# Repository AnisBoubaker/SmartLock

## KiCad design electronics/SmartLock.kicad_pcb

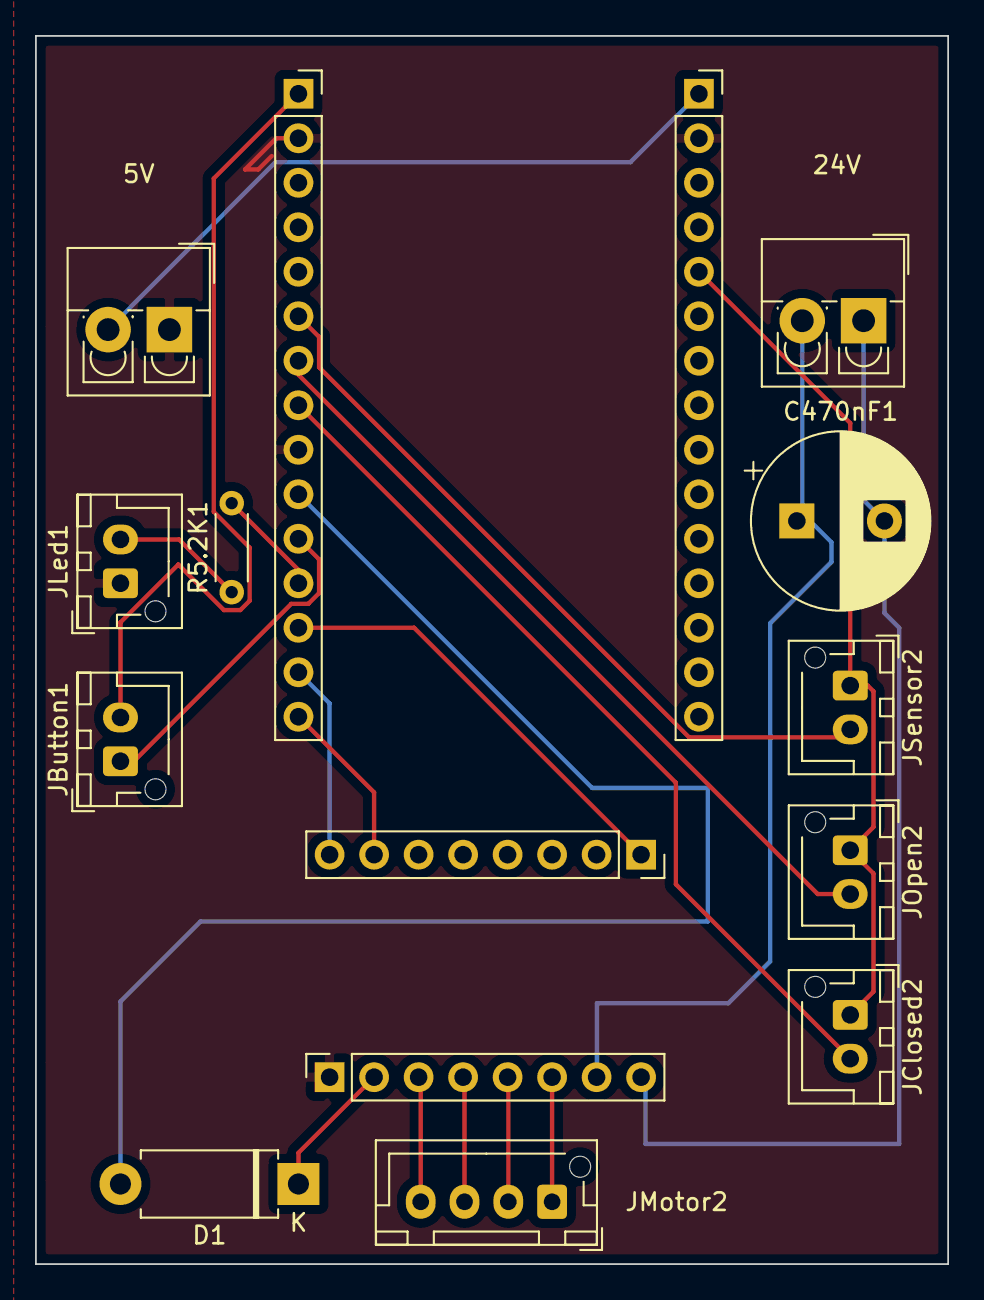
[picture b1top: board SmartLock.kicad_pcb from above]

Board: 2 copper layers, 52.1 x 70.1 mm, 15 parts (0 on the bottom side), 21 nets.

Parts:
5V: 5V; TerminalBlock_4Ucon_1x02_P3.50mm_Vertical
24V: 24V; TerminalBlock_4Ucon_1x02_P3.50mm_Vertical
C470nF1: CP; CP_Radial_D10.0mm_P5.00mm
D1: D_Zener; D_DO-15_P10.16mm_Horizontal
JButton1: Button; JST_XH_B2B-XH-AM_1x02_P2.50mm_Vertical
JClosed2: ClosedS; JST_XH_B2B-XH-AM_1x02_P2.50mm_Vertical
JLed1: Led; JST_XH_B2B-XH-AM_1x02_P2.50mm_Vertical
JMotor2: Motor; JST_XH_B4B-XH-AM_1x04_P2.50mm_Vertical
JOpen2: OpenS; JST_XH_B2B-XH-AM_1x02_P2.50mm_Vertical
JSensor2: Sensor; JST_XH_B2B-XH-AM_1x02_P2.50mm_Vertical
MCU_1: Vin; PinSocket_1x15_P2.54mm_Vertical
MCU_2: 3.3V; PinSocket_1x15_P2.54mm_Vertical
R5.2K1: R_Small; R_Axial_DIN0204_L3.6mm_D1.6mm_P5.08mm_Horizontal
TMC2208_1: En; PinSocket_1x08_P2.54mm_Vertical
TMC2208_2: VM; PinSocket_1x08_P2.54mm_Vertical

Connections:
+5V: 5V.2, MCU_1.1
+24V: 24V.2, C470nF1.1, TMC2208_2.7
GND: 5V.1, JLed1.1, MCU_1.2, MCU_2.2, MCU_2.9, TMC2208_2.1
GND2: 24V.1, C470nF1.2, TMC2208_2.8
unnamed: D1.1, TMC2208_2.2
unnamed: D1.2, MCU_2.10
unnamed: JButton1.1, MCU_2.11
unnamed: JButton1.2, MCU_2.1
unnamed: JClosed2.1, JOpen2.1, JSensor2.1, MCU_1.5
unnamed: JClosed2.2, MCU_2.8
unnamed: JLed1.2, R5.2K1.1
unnamed: JMotor2.1, TMC2208_2.6
unnamed: JMotor2.2, TMC2208_2.5
unnamed: JMotor2.3, TMC2208_2.4
unnamed: JMotor2.4, TMC2208_2.3
unnamed: JOpen2.2, MCU_2.7
unnamed: JSensor2.2, MCU_2.6
unnamed: MCU_2.12, R5.2K1.2
unnamed: MCU_2.13, TMC2208_1.1
unnamed: MCU_2.14, TMC2208_1.8
unnamed: MCU_2.15, TMC2208_1.7

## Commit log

2021-12-29 Added PCB design
2022-01-06 Version 1
